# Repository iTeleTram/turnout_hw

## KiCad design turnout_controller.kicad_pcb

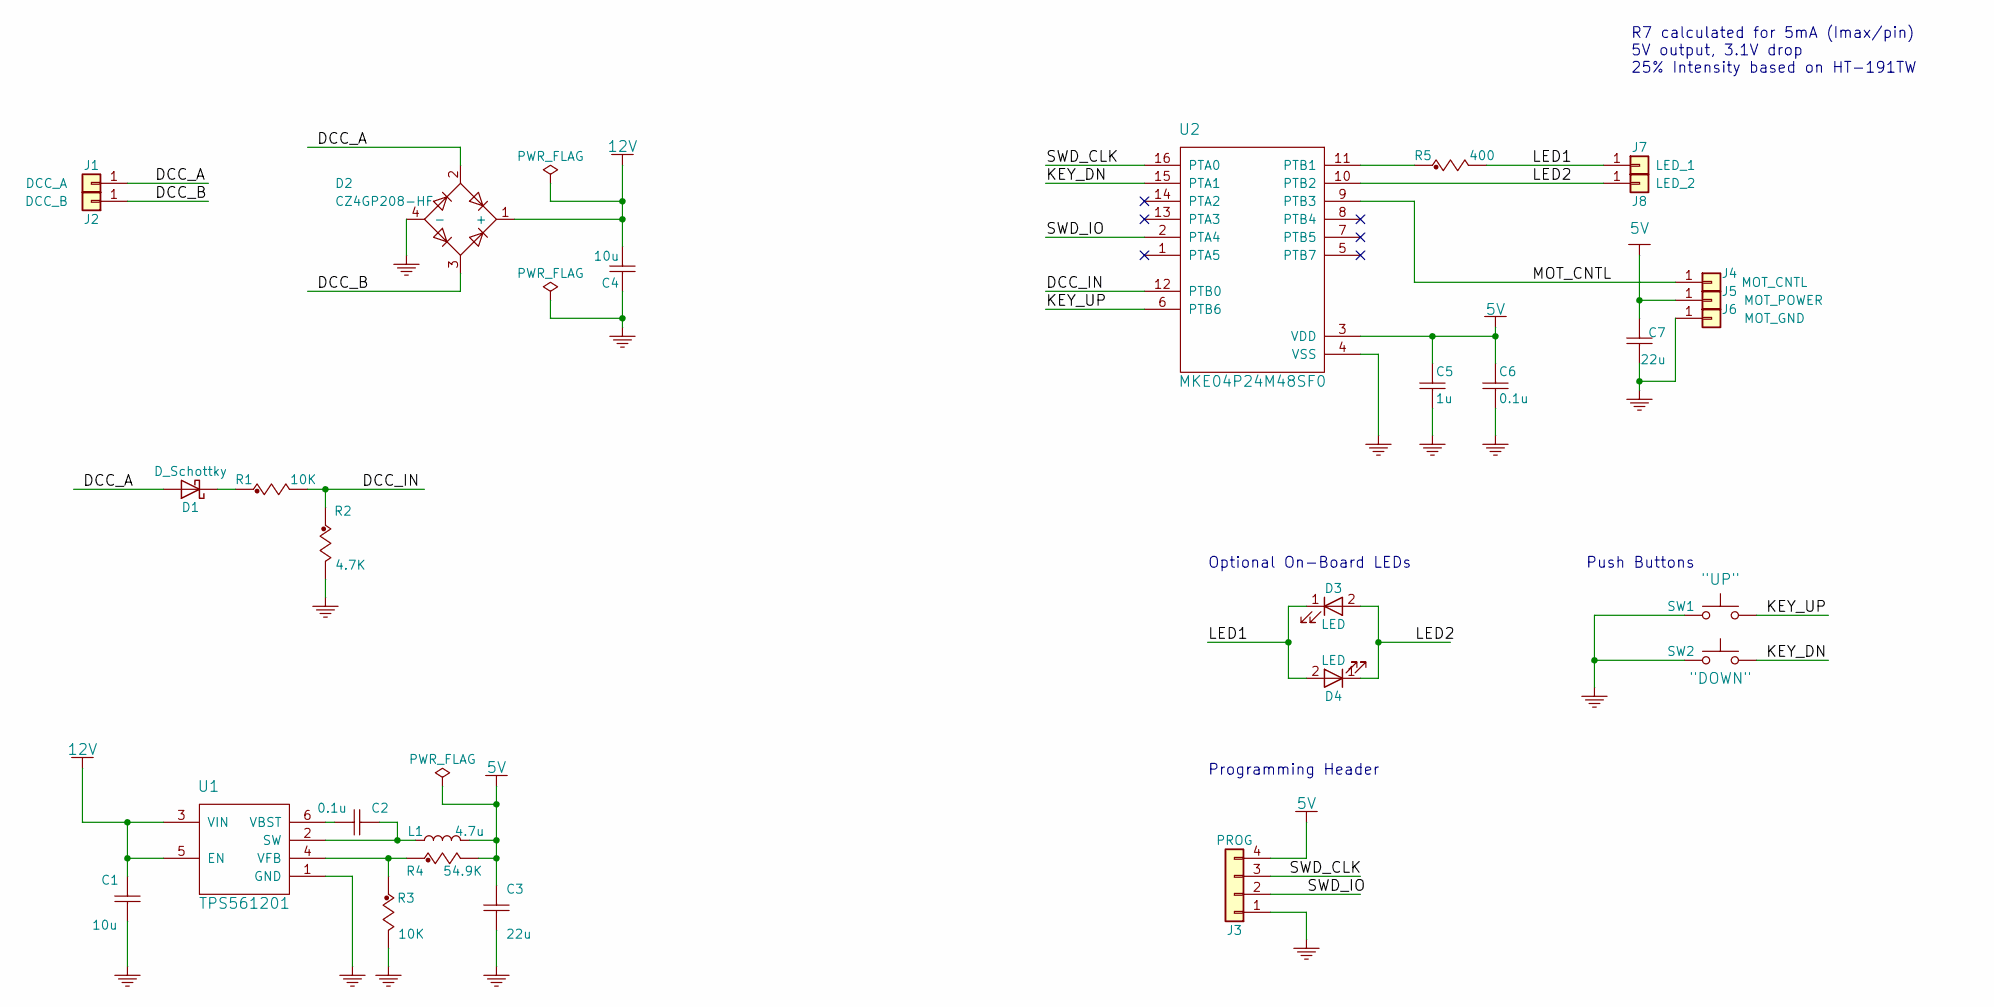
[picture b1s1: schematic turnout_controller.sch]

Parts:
C1, C4: 10u; C_0603_HandSoldering; Voltage 16; MFG P/N GRT188R61C106ME13D
C2: 0.1u; C_0603_HandSoldering; Voltage 10 VDC; MFG P/N VJ0603V104ZXQPW1BC
C3, C7: 22u; C_0603_HandSoldering; Voltage 6.3; MFG P/N GRT188R60J226ME13D
C5: 1u; C_0603_HandSoldering; Voltage 10; MFG P/N 885012106010
C6: 0.1u; C_0603_HandSoldering; Voltage 10; MFG P/N VJ0603V104ZXQPW1BC
D1: D_Schottky; D_SOD-523; MFG P/N PMEG2010AEB,115
D2: CZ4GP208-HF; Z4GP208-HF-SMD; MFG P/N Z4GP208-HF
D3, D4: LED; LED_0603; MFG P/N HT-191TW
J1: DCC_A; Socket_Strip_Straight_1x01_Pitch1.27mm_at_edge
J2: DCC_B; Socket_Strip_Straight_1x01_Pitch1.27mm_at_edge
J3: PROG; Socket_Strip_Straight_1x04_Pitch1.27mm_at_edge
J4: MOT_CNTL; Socket_Strip_Straight_1x01_Pitch1.27mm_at_edge
J5: MOT_POWER; Socket_Strip_Straight_1x01_Pitch1.27mm_at_edge
J6: MOT_GND; Socket_Strip_Straight_1x01_Pitch1.27mm_at_edge
J7: LED_1; Socket_Strip_Straight_1x01_Pitch1.27mm_at_edge
J8: LED_2; Socket_Strip_Straight_1x01_Pitch1.27mm_at_edge
L1: 4.7u; L_Taiyo-Yuden_NR-30xx; MFG P/N NRH3012T4R7MN
R1, R3: 10K; R_0603_HandSoldering; MFG P/N CRCW060310K0JNEAC
R2: 4.7K; R_0603_HandSoldering; MFG P/N CRCW06034K70JNEAC‎
R4: 54.9K; R_0603_HandSoldering; MFG P/N ERA-3AED5492V
R5: 400; R_0603_HandSoldering; MFG P/N PAT0603E4000BST1
SW1: SW_Push; HTB1-Button; MFG P/N TS-1289VE-4
SW2: SW_Push; HTB1-Button
U1: TPS561201; SOT-23-6_Handsoldering; MFG P/N TPS561201DDCR
U2: MKE04P24M48SF0; TSSOP-16_4.4x5mm_Pitch0.65mm; MFG P/N MKE04P24M48SF0

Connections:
5V: C3.2, C5.2, C6.2, C7.1, J3.4, J5.1, L1.2, R4.2, U2.3 (VDD)
12V: C1.2, C4.1, D2.1 (+), U1.3 (VIN), U1.5 (EN)
/DCC_A: D1.2 (A), D2.2, J1.1
/DCC_B: D2.3, J2.1
/DCC_IN: R1.2, R2.1, U2.12 (PTB0)
/KEY_DN: SW2.2, U2.15 (PTA1)
/KEY_UP: SW1.2, U2.6 (PTB6)
/LED1: D3.1 (K), D4.2 (A), J7.1, R5.2
/LED2: D3.2 (A), D4.1 (K), J8.1, U2.10 (PTB2)
/MOT_CNTL: J4.1, U2.9 (PTB3)
/SWD_CLK: J3.3, U2.16 (PTA0)
/SWD_IO: J3.2, U2.2 (PTA4)
GND: C1.1, C3.1, C4.2, C5.1, C6.1, C7.2, D2.4 (-), J3.1, J6.1, R2.2, R3.2, SW1.1, SW2.1, U1.1 (GND), U2.4 (VSS)
unnamed: C2.1, U1.6 (VBST)
unnamed: C2.2, L1.1, U1.2 (SW)
unnamed: D1.1 (K), R1.1
unnamed: R3.1, R4.1, U1.4 (VFB)
unnamed: R5.1, U2.11 (PTB1)

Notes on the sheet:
R7 calculated for 5mA (Imax/pin) 5V output, 3.1V drop 25% Intensity based on HT-191TW
Optional On-Board LEDs
Push Buttons
Programming Header

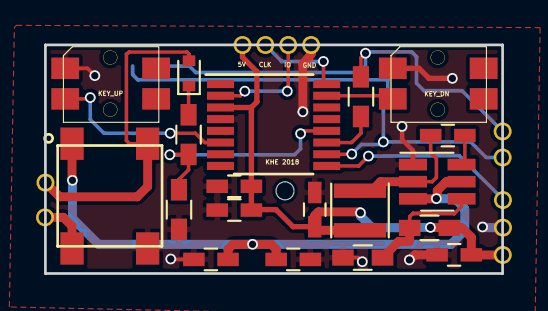
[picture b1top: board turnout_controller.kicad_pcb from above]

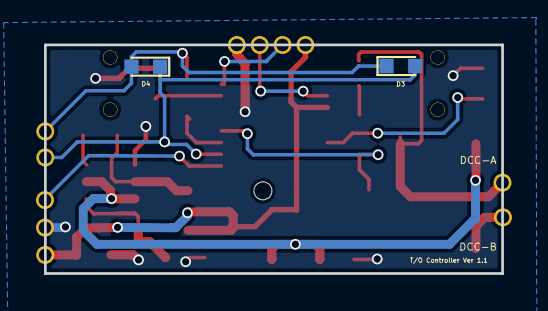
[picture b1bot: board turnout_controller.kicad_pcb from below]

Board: 2 copper layers, 25.4 x 12.7 mm, 29 parts (2 on the bottom side), 18 nets.

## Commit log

2017-11-22 Initial upload of turnout circuit
2017-11-27 Version 2: Passive components not yet defined.
2017-11-27 changed pushbuttons connectivity
2017-11-29 Corrected LED Resistor value and added note. Rearranged schematic
2018-01-03 Updated turnout controller
2018-02-27 Includes:
    New project file
    Footprints for buttons, bridge rectifier and edge connectors
    initial circuit board layout
2018-03-11 1. New PCB layout based around new positioning of buttons.
    2. Optimizing distance between buck circuit components.
    3. Added optional on-board LEDs.
2018-03-19 updated PCB layout
2018-03-20 Updated PCB layout. Re-arrange buck, and added mounting hole
2018-03-23 Connector improvements. Initial trace layout.
2018-03-27 First layout. Connections routed. Ground fill remains.
2018-03-28 DRC fixes (via moved, trace modified. No GND connections.
2018-04-26 Updated PCB layout w/fill zones. Requires mouting hole and pads
2018-05-10 PCB updated with better copper pours, mounting hole and soldering pads
2018-06-25 Circuit updated with TPS561201 buck
2018-06-25 Circuit updated with TPS561201 buck-bug fix C4 value to .1u
2018-07-07 New PCB layout
2018-07-07 to be verified
2018-07-09 alternate PCB 2
2018-07-10 TPS561201 Revision 2
2018-07-10 TPS561201 - final board for review
2018-07-10 TPS561201 - final board for review - added mounting pads
2018-07-15 Holes replaced with via part using proper via sitching techniques.
2018-07-15 Via updated with solid connection
2018-07-23 Board revision 3.0 - prog header @ top
2018-07-29 Fix LED2 via acute angle issue
2018-07-29 File cleanup
2018-08-02 Silk Screen update. Final change before production
2018-08-02 Submitted for production
2018-08-06 Updated schematic for clarity. New Netlist. No PCB changes.
2018-08-17 Added component part numbers (including passives) and BOM.
2018-10-30 Updated schematics and board layout to fix LED issue
2018-10-31 Modified DCC-IN trace to respect 0.25mm clearance requirements from mfg
